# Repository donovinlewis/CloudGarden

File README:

This repository contains the ongoing work to develop code for a wireless soil moisture sensor.

For the Device section, make sure to select Arduino Uno or Pro Mini as the Board with the 
Arduino add-on installed to ensure correct compilation.

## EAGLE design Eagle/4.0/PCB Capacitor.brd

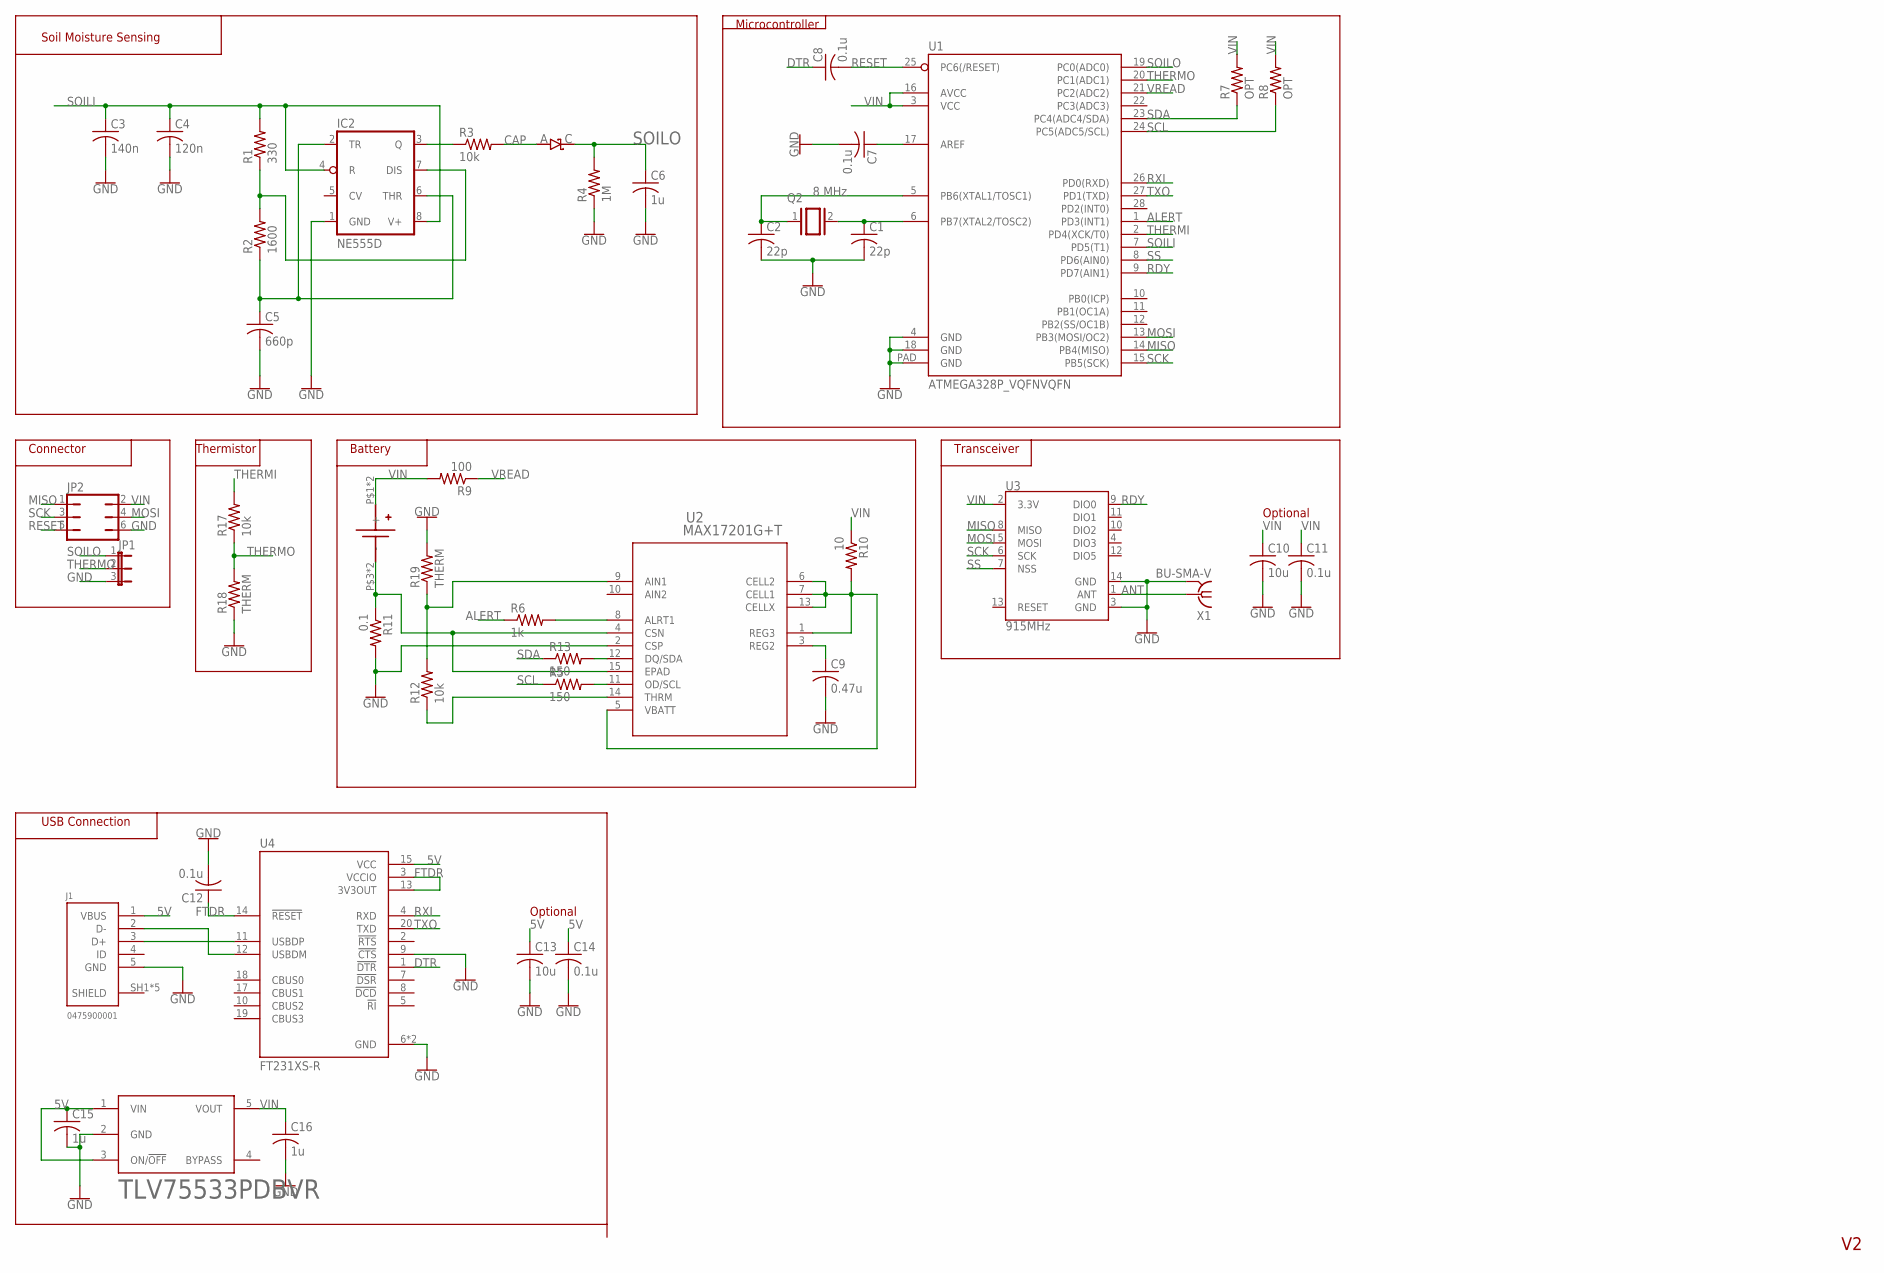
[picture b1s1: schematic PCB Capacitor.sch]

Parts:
C1, C2: 22p; C0805
C3: 140n; C0805
C4: 120n; C0805
C5: 660p; C0805
C6, C15, C16: 1u; C0805
C7, C8, C11, C12, C14: 0.1u; C0805
C9: 0.47u; C0805
C10, C13: 10u; C0805
D11: DIODE_SCHOTTKY_CMMSH2-40; SOD-123
IC2: NE555D; SO08
J1: 0475900001
JP1: JP2E; JP2
JP2: JP3Q
Q2: 8 MHz; QS
R1: 330; R0603
R2: 1600; R0603
R3, R12, R17: 10k; R0603
R4: 1M; R0603
R5, R13: 150; R0603
R6: 1k; R0603
R7, R8: OPT; R0603
R9: 100; R0603
R10: 10; R0603
R11: 0.1; R0603
R18, R19: THERM; R0603
TLV75533PDBVR: LP2985-33DBVR; SOT-23-5
U1: ATMEGA328P_VQFNVQFN; VQFN-28
U2: MAX17201G+T; 21-0137_T1433-2C_MXM
U3: 915MHz; RFM69CW-XXXS2
U4: FT231XS-R; SOP63P599X175-20N
U$1: KEYESTONE_53A_TYPE; KEYESTONE_53_A_TYPE
X1: BU-SMA-V

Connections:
5V: C13.1, C14.1, C15.1, J1.1 (VBUS), TLV75533PDBVR.1 (VIN), TLV75533PDBVR.3 (ON/!OFF!), U4.15 (VCC)
ALERT: R6.1, U1.1 (PD3(INT1))
ANT: U3.1 (ANT), X1.1
CAP: D11.A, R3.2
DTR: C8.1, U4.1 (!DTR)
FTDR: C12.1, U4.3 (VCCIO), U4.13 (3V3OUT), U4.14 (!RESET)
GND: C1.2, C2.2, C3.2, C4.2, C5.2, C6.2, C7.2, C9.2, C10.2, C11.2, C12.2, C13.2, C14.2, C15.2, C16.2, IC2.1 (GND), J1.5 (GND), JP1.3, JP2.6, R4.1, R11.2, R18.1, R19.2, TLV75533PDBVR.2 (GND), U1.4 (GND), U1.18 (GND), U1.PAD (GND), U2.2 (CSP), U3.3 (GND), U3.14 (GND), U4.6 (GND), U4.9 (!CTS), U4.16 (GND), X1.2, X1.3 (2), X1.4 (2), X1.5 (2)
MISO: JP2.1, U1.14 (PB4(MISO)), U3.8 (MISO)
MOSI: JP2.4, U1.13 (PB3(MOSI/OC2)), U3.5 (MOSI)
unnamed: R12.1, U2.14 (THRM)
unnamed: IC2.7 (DIS), R1.1, R2.2
unnamed: C5.1, IC2.2 (TR), IC2.6 (THR), R2.1
unnamed: R11.1, U2.4 (CSN), U2.15 (EPAD), U$1.P$3 (-), U$1.P$4 (-)
unnamed: C9.1, U2.3 (REG2)
unnamed: C1.1, Q2.2, U1.6 (PB7(XTAL2/TOSC2))
unnamed: C2.1, Q2.1, U1.5 (PB6(XTAL1/TOSC1))
unnamed: J1.2 (D-), U4.12 (USBDM)
unnamed: IC2.3 (Q), R3.1
unnamed: J1.3 (D+), U4.11 (USBDP)
unnamed: C7.1, U1.17 (AREF)
unnamed: R10.2, U2.1 (REG3), U2.5 (VBATT), U2.6 (CELL2), U2.7 (CELL1), U2.13 (CELLX)
unnamed: R12.2, R19.1, U2.9 (AIN1)
unnamed: R6.2, U2.8 (ALRT1)
unnamed: R13.2, U2.12 (DQ/SDA)
unnamed: R5.2, U2.11 (OD/SCL)
RDY: U1.9 (PD7(AIN1)), U3.9 (DIO0)
RESET: C8.2, JP2.5, U1.25 (PC6(/RESET))
RXI: U1.26 (PD0(RXD)), U4.4 (RXD)
SCK: JP2.3, U1.15 (PB5(SCK)), U3.6 (SCK)
SCL: R5.1, R8.1, U1.24 (PC5(ADC5/SCL))
SDA: R7.1, R13.1, U1.23 (PC4(ADC4/SDA))
SHIELD: J1.SH1 (SHIELD), J1.SH2 (SHIELD), J1.SH3 (SHIELD), J1.SH4 (SHIELD), J1.SH5 (SHIELD)
SOILI: C3.1, C4.1, IC2.4 (R), IC2.8 (V+), R1.2, U1.7 (PD5(T1))
SOILO: C6.1, D11.C, JP1.1, R4.2, U1.19 (PC0(ADC0))
SS: U1.8 (PD6(AIN0)), U3.7 (NSS)
THERMI: R17.2, U1.2 (PD4(XCK/T0))
THERMO: JP1.2, R17.1, R18.2, U1.20 (PC1(ADC1))
TXO: U1.27 (PD1(TXD)), U4.20 (TXD)
VIN: C10.1, C11.1, C16.1, JP2.2, R7.2, R8.2, R9.2, R10.1, TLV75533PDBVR.5 (VOUT), U1.3 (VCC), U1.16 (AVCC), U3.2 (3.3V), U$1.P$1 (+), U$1.P$2 (+)
VREAD: R9.1, U1.21 (PC2(ADC2))

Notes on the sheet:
Connector
Soil Moisture Sensing
Thermistor
Microcontroller
Battery
Optional
Transceiver
USB Connection

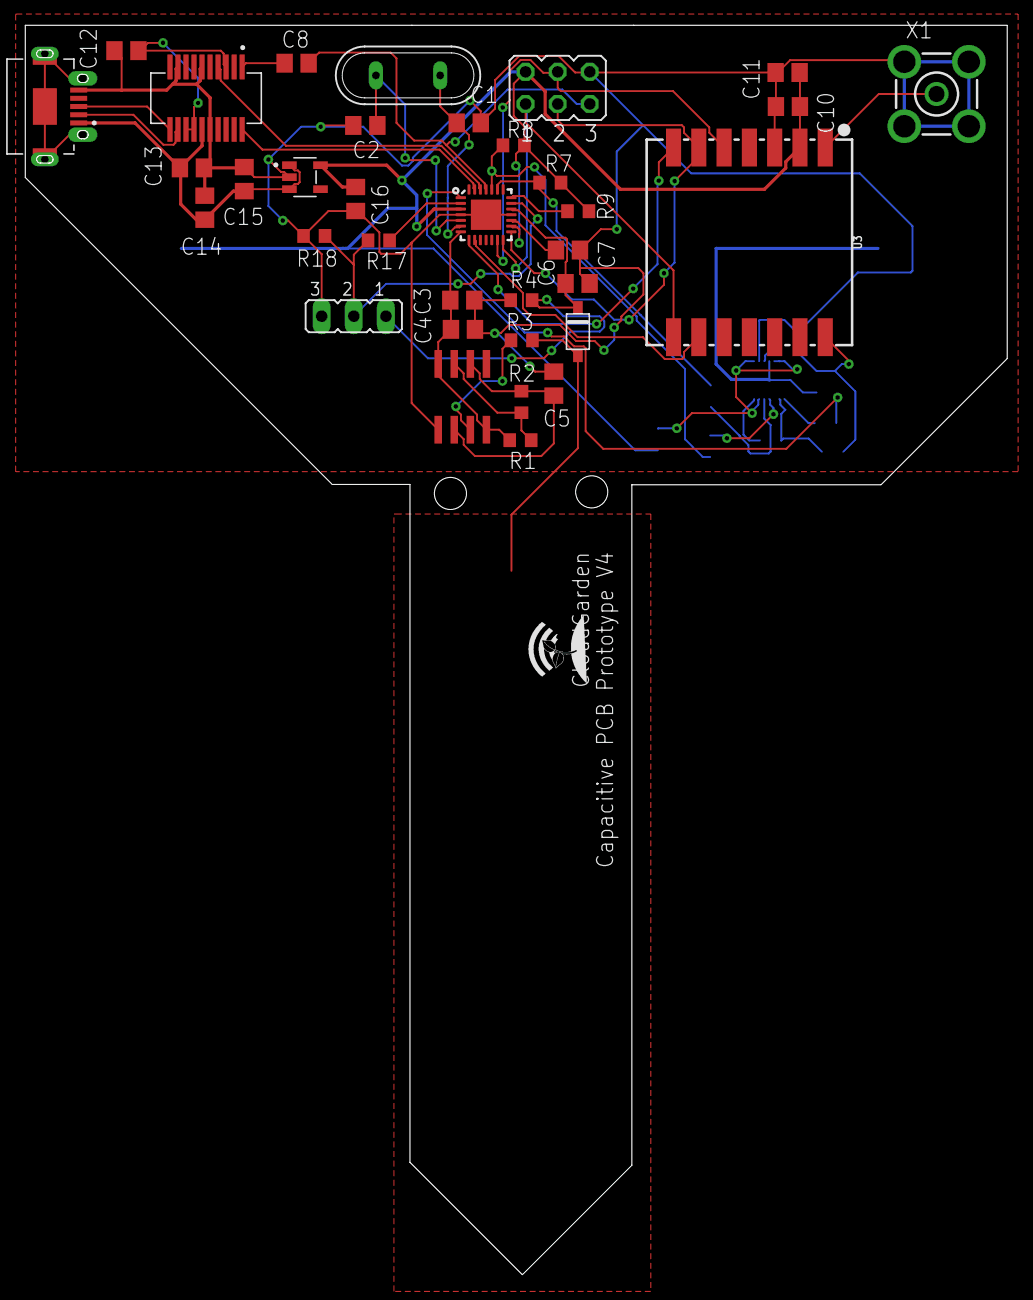
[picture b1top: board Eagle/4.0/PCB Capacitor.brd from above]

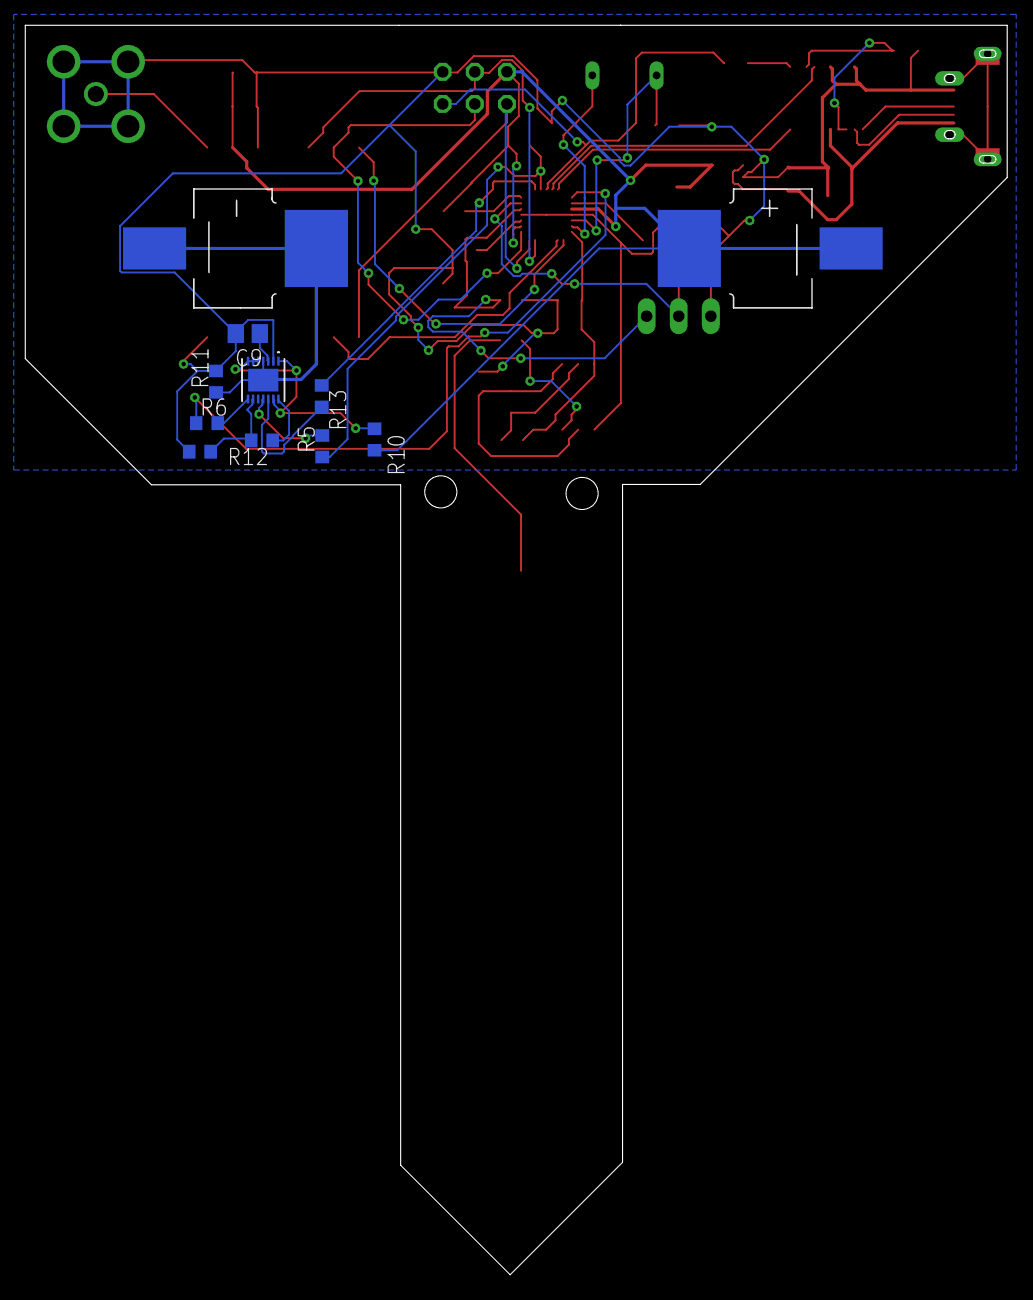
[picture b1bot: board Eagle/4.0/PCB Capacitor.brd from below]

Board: 2 copper layers, 77.7 x 98.8 mm, 45 parts (10 on the bottom side), 40 nets.

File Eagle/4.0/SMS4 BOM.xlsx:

Soil Moisture Sensor V4.1 |  |  | 44228
Qty | Value | Device | Parts | Digikey Part Number | Digikey Price | Itemized | Total
1 |  | JP2E | JP1 | HDR100IMP40M-G-V-TH-ND | 0.69 | 0.69 | 34.370000000000005
1 |  | JP3Q | JP2 |  |  | 0
1 | 0.1 | R-US_R0603 | R11 | A103277CT-ND | 0.23 | 0.23
6 | 0.1u | C-USC0805 | C7, C8, C11, C12, C14 | 1276-1099-1-ND | 0.1 | 0.60000000000000009
1 | 0.47u | C-USC0805 | C9 | 1276-6480-1-ND | 0.1 | 0.1
1 | 1M | R-US_R0603 | R4 | 541-CRCW06031M00JNEACCT-ND | 0.1 | 0.1
1 | 1k | R-US_R0603 | R14 | 541-3949-1-ND | 0.1 | 0.1
3 | 1u | C-USC0805 | C6, C15, C16 | 1276-1026-1-ND | 0.1 | 0.30000000000000004
1 | 8 MHz | XTAL/S | Q2 | 2151-AS-8.000-18-SMD-TRCT-ND | 0.19 | 0.19
1 | 10 | R-US_R0603 | R10 | 13-RE0603FRE0710RLCT-ND | 0.1 | 0.1
3 | 10k | R-US_R0603 | R3 | 541-5136-1-ND | 0.1 | 0.30000000000000004
3 | 10u | C-USC0805 | C10, C13 | 1276-6455-1-ND | 0.11 | 0.33
2 | 22p | C-USC0805 | C1, C2 | 1276-1047-1-ND | 0.1 | 0.2
1 | 100 | R-US_R0603 | R9 | 541-3951-1-ND | 0.1 | 0.1
1 | 120n | C-USC0805 | C4 | 399-9171-1-ND | 0.13 | 0.13
1 | 140n | C-USC0805 | C3 | 732-8040-1-ND | 0.1 | 0.1
2 | 150 | R-US_R0603 | R15, R16 | 541-4023-1-ND | 0.1 | 0.2
1 | 330 | R-US_R0603 | R1 | 541-CRCW0603330RFKEBCCT-ND | 0.1 | 0.1
1 | 660p | C-USC0805 | C5 | 732-8067-1-ND | 0.1 | 0.1
1 | 915MHz | RFM69CW-915MHZ | U3 | 1568-1394-ND | 5.95 | 5.95
1 | 1600 | R-US_R0603 | R2 | 541-5237-1-ND | 0.1 | 0.1
1 | 475900001 | 475900001 | J1 | 2057-MCR-B-S-RA-SMT-CS5A-NF-T/RCT-ND | 0.34 | 0.34
1 | ATMEGA328P_VQFNVQFN | ATMEGA328P_VQFNVQFN | U1 | ATMEGA328P-MMH-ND | 2.4300000000000002 | 2.4300000000000002
1 | BU-SMA-V | BU-SMA-V | X1 | 2057-RF2-04A-T-00-50-G-ND | 1.29 | 1.29
1 | DIODE_SCHOTTKY_CMMSH2-40 | DIODE_SCHOTTKY_CMMSH2-40 | D11 | 1727-7328-1-ND | 0.13 | 0.13
1 | FT231XS-R | FT231XS-R | U4 | 768-1129-1-ND | 2.12 | 2.12
2 | KEYESTONE_53A_TYPE | KEYESTONE_53A_TYPE | U$1 | 36-53-ND | 0.33 | 0.66
1 | LP2985-33DBVR | LP2985-33DBVR | TLV75533PDBVR | 296-50411-1-ND | 0.42 | 0.42
1 | MAX17201G+T | MAX17201G+T | U2 | MAX17201G+TCT-ND | 3.85 | 3.85
1 | NE555D | NE555D | IC2 | 296-6501-1-ND | 0.41 | 0.41
2 | THERM | R-US_R0603 | R6, R12 | 490-16279-1-ND | 0.1 | 0.2
0.2 | PCB |  |  | PCB Manufacturer | 5 | 1
1 | Antenna |  | ANT | 939-9000962-XLPDNW-ND | 3.95 | 3.95
1 | Battery |  | BAT | 1908-ER17505J-SA-ND | 7.55 | 7.55

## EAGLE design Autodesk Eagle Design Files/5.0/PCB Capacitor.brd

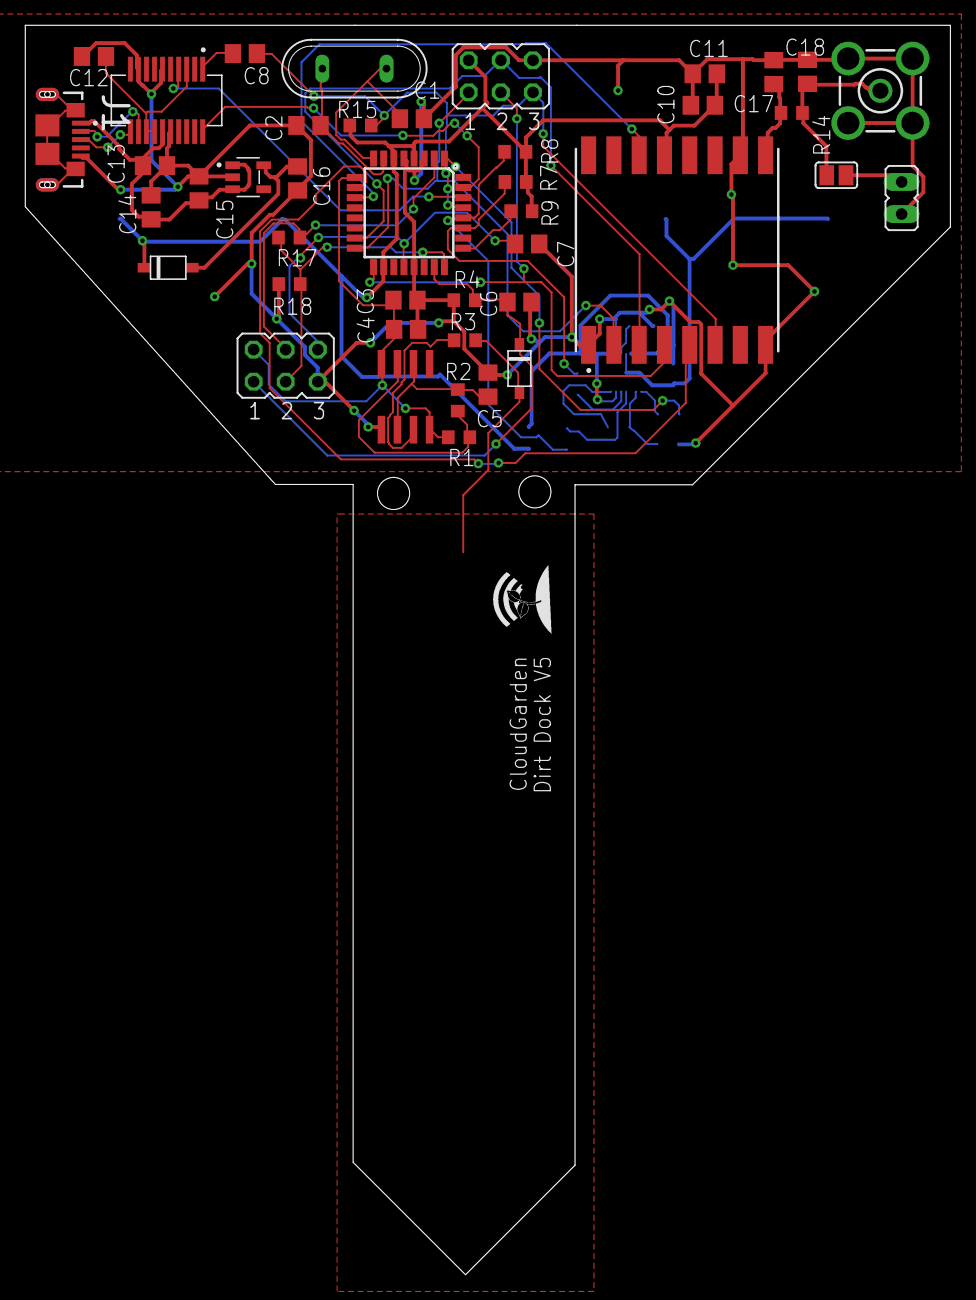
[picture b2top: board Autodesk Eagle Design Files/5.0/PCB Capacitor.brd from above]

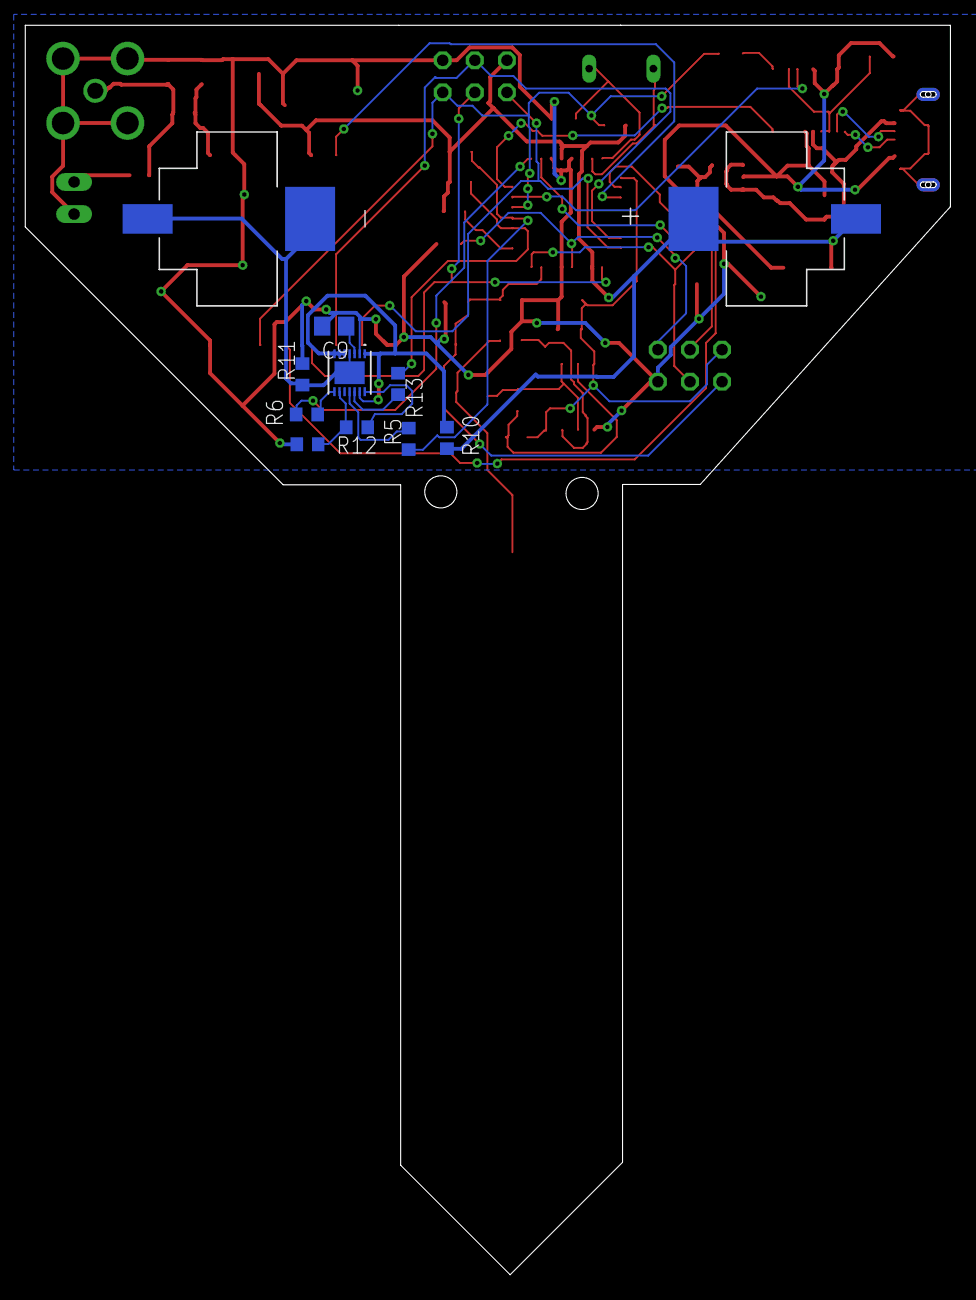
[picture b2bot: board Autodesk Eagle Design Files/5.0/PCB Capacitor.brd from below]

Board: 2 copper layers, 73.2 x 98.8 mm, 52 parts (10 on the bottom side), 43 nets.

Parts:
BT2: BK-53; BAT_BK-53
C1, C2: 22p; C0805
C3: 140n; C0805
C4: 120n; C0805
C5: 660p; C0805
C6, C15, C16: 1u; C0805
C7, C8, C11, C12, C14: 0.1u; C0805
C9: 0.47u; C0805
C10, C13: 10u; C0805
C17, C18: opt; C0805
D1, D11: DIODE_SCHOTTKY_CMMSH2-40; SOD-123
IC2: NE555D; SO08
J1: USB3076-XX-X_REVC; GCT_USB3076-XX-X_REVC
JP2, JP5: JP3Q
JP3: JP1
Q2: 8 MHz; QS
R1: 330; R0603
R2: 1600; R0603
R3, R12, R17: 10k; R0603
R4: 1M; R0603
R5, R13: 150; R0603
R6: 1k; R0603
R7, R8, R15: OPT; R0603
R9: 100; R0603
R10: 10; R0603
R11: 0.1; R0603
R14: opt; R0603
R18, R19: THERM; R0603
SJ1: SJ
TLV75533PDBVR: LP2985-33DBVR; SOT-23-5
U1: COM-13909; MOD_COM-13909
U2: MAX17201G+T; 21-0137_T1433-2C_MXM
U4: FT231XS-R; SOP63P599X175-20N
U5: ATMEGA328P_TQFP; TQFP32-08
X1: BU-SMA-V

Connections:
5V: C13.1, C14.1, C15.1, J1.1, TLV75533PDBVR.1, TLV75533PDBVR.3, U4.15
ALERT: R6.1, U5.1
ANTEX: JP3.1, SJ1.2
AREF: C7.1, JP5.6, U5.20
CAP: D11.A, R3.2
DTR: C8.1, U4.1
FTDR: C12.1, U4.3, U4.13, U4.14
GND: C1.2, C2.2, C3.2, C4.2, C5.2, C6.2, C7.2, C9.2, C10.2, C11.2, C12.2, C13.2, C14.2, C15.2, C16.2, C17.2, C18.2, IC2.1, J1.5, JP2.6, JP3.2, JP5.5, R4.1, R11.2, R18.1, R19.2, TLV75533PDBVR.2, U1.1, U1.8, U1.10, U2.2, U4.6, U4.9, U4.16, U5.3, U5.5, U5.21, X1.2, X1.3, X1.4, X1.5
MISO: JP2.1, U1.2, U5.16
MOSI: JP2.4, U1.3, U5.15
unnamed: R12.1, U2.14
unnamed: IC2.7, R1.1, R2.2
unnamed: C5.1, IC2.2, IC2.6, R2.1
unnamed: BT2.1-, BT2.2-, R11.1, U2.4, U2.15
unnamed: C9.1, U2.3
unnamed: C1.1, Q2.2, U5.8
unnamed: C2.1, Q2.1, U5.7
unnamed: J1.2, U4.12
unnamed: IC2.3, R3.1
unnamed: J1.3, U4.11
unnamed: R10.2, U2.1, U2.5, U2.6, U2.7, U2.13
unnamed: R12.2, R19.1, U2.9
unnamed: R6.2, U2.8
unnamed: R13.2, U2.12
unnamed: R5.2, U2.11
unnamed: C16.1, D1.A, TLV75533PDBVR.5
unnamed: C18.1, R14.2, SJ1.1, X1.1
unnamed: C17.1, R14.1, U1.9
RDY: U1.14, U5.11
RESET: C8.2, JP2.5, R15.1, U1.6, U5.29
RXI: U4.4, U5.30
SCK: JP2.3, U1.4, U5.17
SCL: R5.1, R8.1, U5.28
SDA: R7.1, R13.1, U5.27
SHIELD: J1.6, J1.7, J1.8, J1.9, J1.10, J1.11
SOILI: C3.1, C4.1, IC2.4, IC2.8, JP5.2, R1.2, U5.9
SOILO: C6.1, D11.C, JP5.1, R4.2, U5.23
SS: U1.5, U5.10
THERMI: JP5.4, R17.2, U5.2
THERMO: JP5.3, R17.1, R18.2, U5.24
TXO: U4.20, U5.31
VIN: BT2.1+, BT2.2+, C10.1, C11.1, D1.C, JP2.2, R7.2, R8.2, R9.2, R10.1, R15.2, U1.13, U5.4, U5.6, U5.18
VREAD: R9.1, U5.25

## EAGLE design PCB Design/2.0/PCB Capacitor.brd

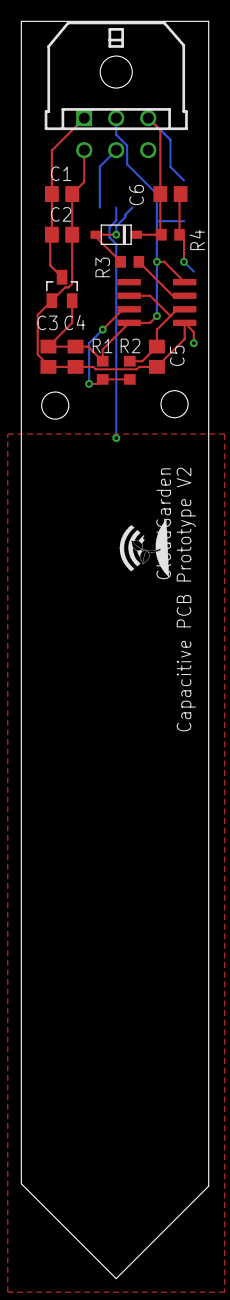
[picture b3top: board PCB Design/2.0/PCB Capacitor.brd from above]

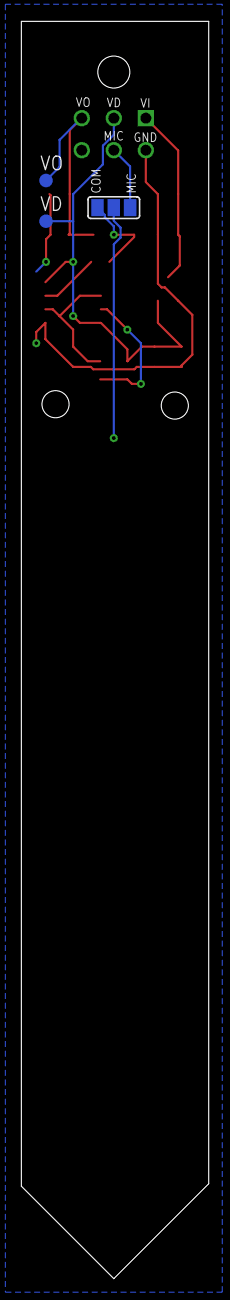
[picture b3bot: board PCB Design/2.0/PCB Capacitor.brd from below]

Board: 2 copper layers, 17.6 x 117.8 mm, 17 parts (3 on the bottom side), 9 nets.

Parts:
C1: 160n; C0805
C2: 10u; C0805
C3: 140n; C0805
C4: 120n; C0805
C5: 660p; C0805
C6: 1u; C0805
D11: DIODE_SCHOTTKY_CMMSH2-40; SOD-123
IC1: MCP1703CB; SOT23
IC2: NE555D; SO08
R1: 330; R0603
R2: 1600; R0603
R3: 10k; R0603
R4: 1M; R0603
SJ1: SJ_2
VD: TPB1,27; B1,27
VO: TPB1,27; B1,27
X1: 43045-0600

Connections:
GND: C1.2, C2.2, C3.2, C4.2, C5.2, C6.2, IC1.1, IC2.1, R4.1, X1.P$4
unnamed: IC2.7, R1.1, R2.2
unnamed: C5.1, IC2.2, IC2.6, R2.1
unnamed: IC2.3, R3.1
SJCOM: D11.A, R3.2, SJ1.1
SJMIC: SJ1.3, X1.P$5
VDIR: C3.1, C4.1, IC1.2, IC2.4, IC2.8, R1.2, VD.TP, X1.P$2
VIN: C1.1, C2.1, IC1.3, X1.P$1
VOUT: C6.1, D11.C, R4.2, VO.TP, X1.P$3

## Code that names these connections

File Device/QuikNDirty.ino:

/* Some bullshit Donovin Lewis made
   Real talk tho

*/

#include "LowPower.h"

//#define LENGTH 9

#define SOILI PD5
#define SOILO PC0

#define THERMI PD4
#define THERMO PC1

int mode = 1;
int cal = 0;
unsigned long durStamp, curSec, duration = 0;

int calAir = 564;
int calWat = 293;
int soilVal, soilPct = 0;

const int A = 1.009249522e-03;
const int B = 2.378405444e-04;
const int C = 2.019202697e-07;

int tempVal = 0;

int battVolts = 0;

void setup() {
  //Serial.begin(9600);

  pinMode(SOILI, OUTPUT);
  pinMode(SOILO, INPUT);

  pinMode(THERMI, OUTPUT);
  pinMode(THERMO, INPUT);
}

void loop() {
  /*
    if (Serial.available() > LENGTH-1) {
      Serial.readBytes(rec_msg, LENGTH);

      //Prints a serial message containing the serial values sent from the master for debugging
      for (int i = 0; i < LENGTH; i++) {
        Serial.print(rec_msg[i], HEX);
        Serial.print(" ");
      }
      Serial.println();
    }
  */

  digitalWrite(SOILI, HIGH);
  digitalWrite(THERMI, HIGH);
  delay(100);

  soilVal = analogRead(SOILI);
  soilPct = map(soilVal, calAir, calWat, 0, 100);

  tempVal = therm(analogRead(THERMO));

  for (int i = 0; i <= 2; i++) battVolts += getBandgap();
  battVolts = battVolts / 3;

  if (mode == 0) duration = 3600;

  if (mode == 1) duration = 5;

  if (mode == 2) {
    duration = 1;
    if (cal == 1) calAir = soilVal;
    if (cal == 2) calWat = soilVal;
    if (cal != 1 || cal != 2) mode = 0;
  }

  durStamp = millis();
  duration  *= 12.5; //Converts to millis with sleep time factored in

  while ((millis() - durStamp) < duration) {
    LowPower.powerDown(SLEEP_8S, ADC_OFF, BOD_OFF);
  }
}

void printVal() {
  curSec = millis() / 1000;
  Serial.print(curSec);
  Serial.print(" , ");
  Serial.print(soilVal);
  Serial.print(" , ");
  Serial.print(soilPct);
  Serial.print(" , ");
  Serial.print(tempVal);
  Serial.print(" , ");
  Serial.println(battVolts);
}

int therm(int V0) {
  float logRT, T, TC, TF = 0;
  logRT = log(10000 * ((1024 / V0) - 1));
  T = (1 / (A + B * logRT + C * logRT * logRT * logRT));
  TC = T - 273.15;
  TF = (TC * 1.8) + 32;
  return TF;
}

int getBG(void) {
  const long InternalReferenceVoltage = 1050L;  // Adust this value to your specific internal BG voltage x1000
  // REFS1 REFS0          --> 0 1, AVcc internal ref.
  // MUX3 MUX2 MUX1 MUX0  --> 1110 1.1V (VBG)
  ADMUX = (0 << REFS1) | (1 << REFS0) | (0 << ADLAR) | (1 << MUX3) | (1 << MUX2) | (1 << MUX1) | (0 << MUX0);
  // Start a conversion
  ADCSRA |= _BV( ADSC );
  // Wait for it to complete
  while ( ( (ADCSRA & (1 << ADSC)) != 0 ) );
  // Scale the value
  int results = (((InternalReferenceVoltage * 1024L) / ADC) + 5L) / 10L;
  return results;
}

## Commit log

2020-10-24 Added initial soil moisture sensing code
2020-11-06 Added CSV Logging Soil Moisture File
2020-11-06 Rename CSVSoilMoist to CSVSoilMoist.ino
2021-01-14 Rename SecondLog/CSVSoilMoist.ino to Soil Moisture Sensing/secondLog_SoilMoist
    Moved into correct folder and changed name to reflect changes
2021-01-14 Added Eagle Files
2021-01-14 Rename Eagle/1.0/Interdigitated.b#1 to Eagle Board Files/1.0/Interdigitated.b#1
    Changed folder name
2021-01-14 Changed back due to issues
2021-01-14 Added data from testing and component calculations
2021-02-02 Added 4.0 version of eagle
2021-02-07 Added Eagle Version 4.2
2021-02-09 Corrected file type
2021-02-09 Changed folder name
2021-02-09 Modified/Renamed folders
2021-02-09 Added new files
2021-02-09 Added cursory files in each folder
2021-02-09 Fixed main.h issues
2021-02-09 Added preliminary sms code
2021-02-10 Modified #define to use const int instead
2021-02-10 Altered to const int instead of define
2021-02-10 Added serial print for testing
2021-02-10 Confirmed functionality of library using c++ libraries
2021-02-10 Modified order
2021-02-10 Annoying Arduino library dependency for redundancy
2021-02-10 Modified README
2021-02-10 Added README for compilation instructions
2021-02-14 Altered Soil Moisture code to be OOP
2021-02-16 added .gitignore
2021-02-16 removed more .vscode stuff
2021-02-16 added initial Transceiver interface
2021-02-17 Added introductory battery monitoring code
2021-02-17 Changed definitions to simplify
2021-02-17 Altered folder name from test code
2021-03-11 added compileable transceiver code
2021-03-16 remove ignored files
2021-03-16 remove license blurb since license has not been added
2021-03-23 added preliminary main function and helper functions; TODO: something about sleep function
2021-04-10 Added Quick and Dirty Sensing
    Soil moisture and temperature sensing mix
2021-04-10 wireless transmission is functional
2021-04-10 Added Battery Stuff
2021-04-10 cleaned up code and pulled in thermistor and battery monitoring changes
2021-04-26 Finish development
2021-04-26 merged changes with local
    Issues with local repository forced branch deletion
2021-04-26 Update batmon.h
    Fixed issues again
2021-04-26 Fixed arduino.h call
2021-04-26 Reorganized to include additional testing code and simplify folder structure
2021-04-26 Rearranged files again
2021-04-26 Rearranged files
2021-04-27 Split files
2021-05-03 Added licensing
2021-05-03 Added Final Report
2021-05-28 Added Open Source License
2021-12-24 Update README.md
    Added description of other product serving the same purpose.
2022-08-14 Added individual report for soil moisture sensing

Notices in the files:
parts and their libraries:
SparkFun-IC-Microcontroller: Licensing: Creative Commons ShareAlike 4.0 International - https://creativecommons.org/licenses/by-sa/4.0
COPYRIGHT: Copyright (C) 2018 Accelerated Designs. All rights reserved
